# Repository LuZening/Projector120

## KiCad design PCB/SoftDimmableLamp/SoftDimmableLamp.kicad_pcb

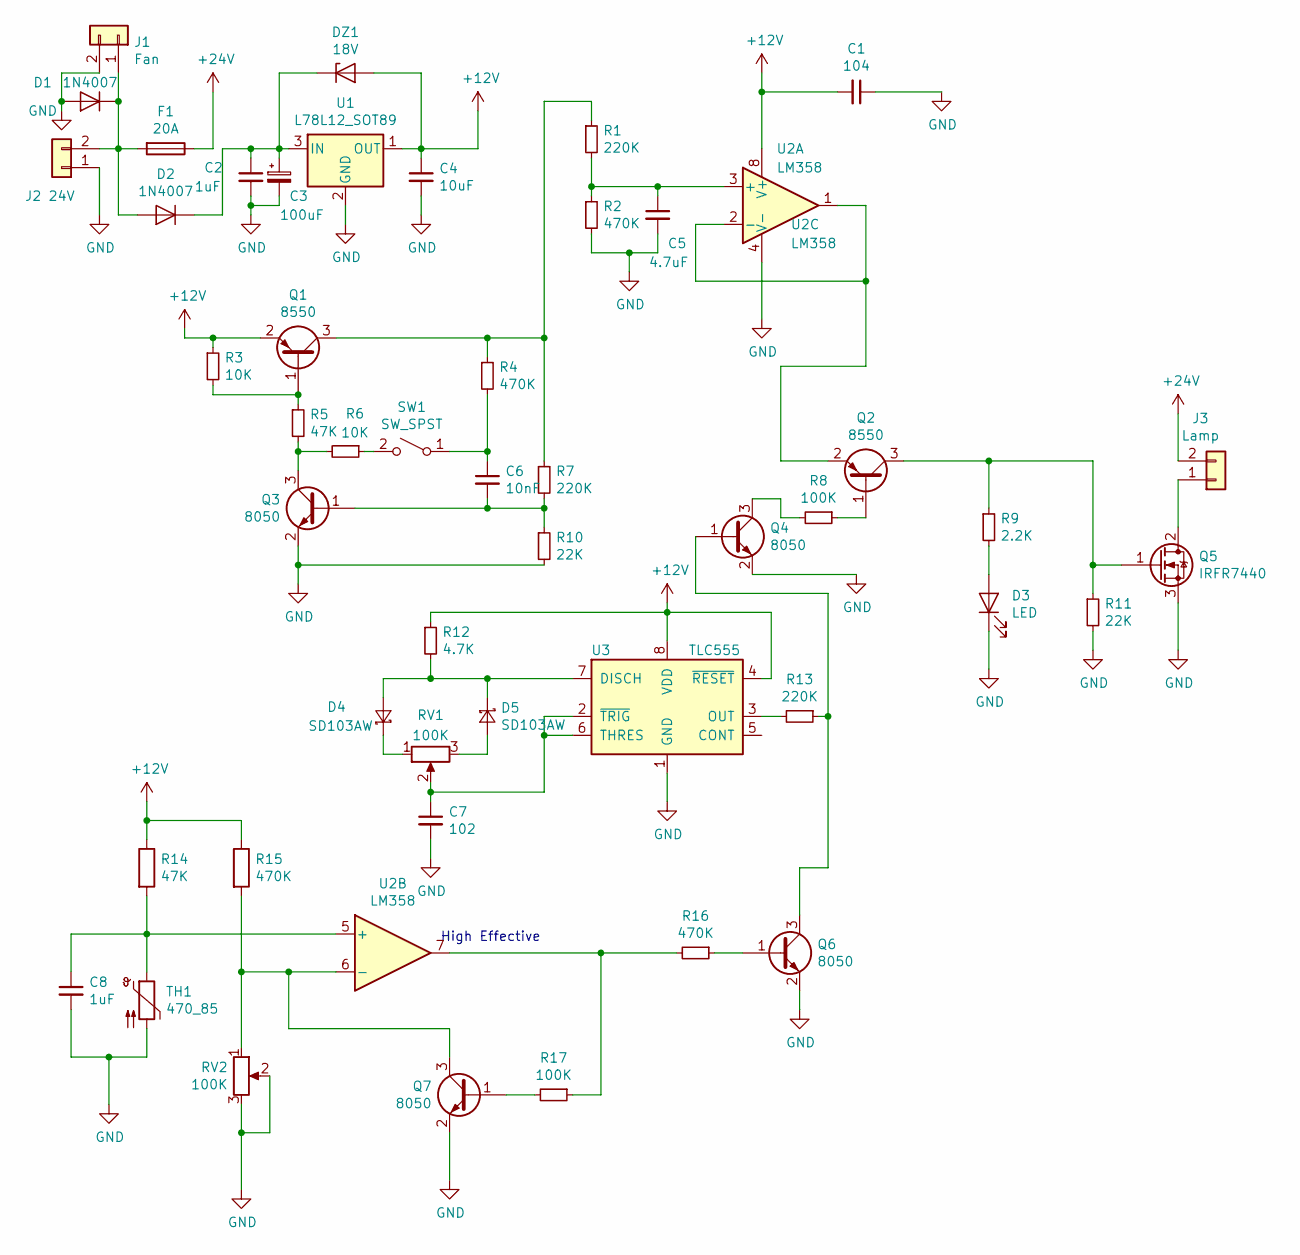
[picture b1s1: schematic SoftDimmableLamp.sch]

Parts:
C1: 104; 0805_C
C2, C8: 1uF; 0805_C
C3: 100uF; CP_Radial_D5.0mm_P2.50mm
C4: 10uF; 0805_C
C5: 4.7uF; 0805_C
C6: 10nF; 0805_C
C7: 102; 0805_C
D1, D2: 1N4007; SMA(DO-214AC)_S2
D3: LED; LED_D3.0mm
D4, D5: SD103AW; SOD-123
DZ1: 18V; LL-34
F1: 20A; FUSE6x32
J1: Fan; Molex_KK-6410-02_02x2.54mm_Straight
J2: 24V; PhoenixContact_GMSTBA-G_02x7.62mm_Angled
J3: Lamp; PhoenixContact_GMSTBA-G_02x7.62mm_Angled
Q1, Q2: 8550; SOT-23(SOT-23-3)
Q3, Q4, Q6, Q7: 8050; SOT-23(SOT-23-3)
Q5: IRFR7440; TO-252-2
R1, R7, R13: 220K; 0805
R2, R4, R15, R16: 470K; 0805
R3, R6: 10K; 0805
R5, R14: 47K; 0805
R8, R17: 100K; 0805
R9: 2.2K; 0805
R10, R11: 22K; 0805
R12: 4.7K; 0805
RV1: 100K; Potentiometer_Alps_RK163_Double_Vertical
RV2: 100K; 3362P
SW1: SW_SPST; PhoenixContact_MSTBA-G_02x5.08mm_Angled
TH1: 470_85; PhoenixContact_MSTBA-G_02x5.08mm_Angled
U1: L78L12_SOT89; SOT-89(SOT-89-3)
U2: LM358; SOIC-8_150MIL
U3: TLC555; SOIC-8_150MIL

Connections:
+12V: C1.2, C4.1, DZ1.1 (A), Q1.2 (E), R3.1, R12.1, R14.1, R15.1, U1.1 (OUT), U2.8 (V+), U3.4 (~RESET), U3.8 (VDD)
+24V: F1.1, J3.2
GND: C1.1, C2.2, C3.2, C4.2, C5.2, C7.2, C8.2, D1.1 (A), D3.1 (K), J1.2, J2.1, Q3.2 (E), Q4.2 (E), Q5.3 (S), Q6.2 (E), Q7.2 (E), R2.2, R10.2, R11.2, RV2.2, RV2.3, TH1.2, U1.2 (GND), U2.4 (V-), U3.1 (GND)
unnamed: C2.1, C3.1, D2.2 (K), DZ1.2 (K), U1.3 (IN)
unnamed: C5.1, R1.2, R2.1, U2.3 (+)
unnamed: C6.1, R4.2, SW1.1 (A)
unnamed: C6.2, Q3.1 (B), R7.2, R10.1
unnamed: C7.1, RV1.2, U3.2 (~TRIG), U3.6 (THRES)
unnamed: C8.1, R14.2, TH1.1, U2.5 (+)
unnamed: D1.2 (K), D2.1 (A), F1.2, J1.1, J2.2
unnamed: D3.2 (A), R9.2
unnamed: D4.1 (A), D5.2 (K), R12.2, U3.7 (DISCH)
unnamed: D4.2 (K), RV1.1
unnamed: D5.1 (A), RV1.3
unnamed: J3.1, Q5.2 (D)
unnamed: Q1.1 (B), R3.2, R5.1
unnamed: Q1.3 (C), R1.1, R4.1, R7.1
unnamed: Q2.1 (B), R8.1
unnamed: Q2.2 (E), U2.1, U2.2 (-)
unnamed: Q2.3 (C), Q5.1 (G), R9.1, R11.1
unnamed: Q3.3 (C), R5.2, R6.2
unnamed: Q4.1 (B), Q6.3 (C), R13.1
unnamed: Q4.3 (C), R8.2
unnamed: Q6.1 (B), R16.1
unnamed: Q7.1 (B), R17.2
unnamed: Q7.3 (C), R15.2, RV2.1, U2.6 (-)
unnamed: R6.1, SW1.2 (B)
unnamed: R13.2, U3.3 (OUT)
unnamed: R16.2, R17.1, U2.7

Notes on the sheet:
High Effective

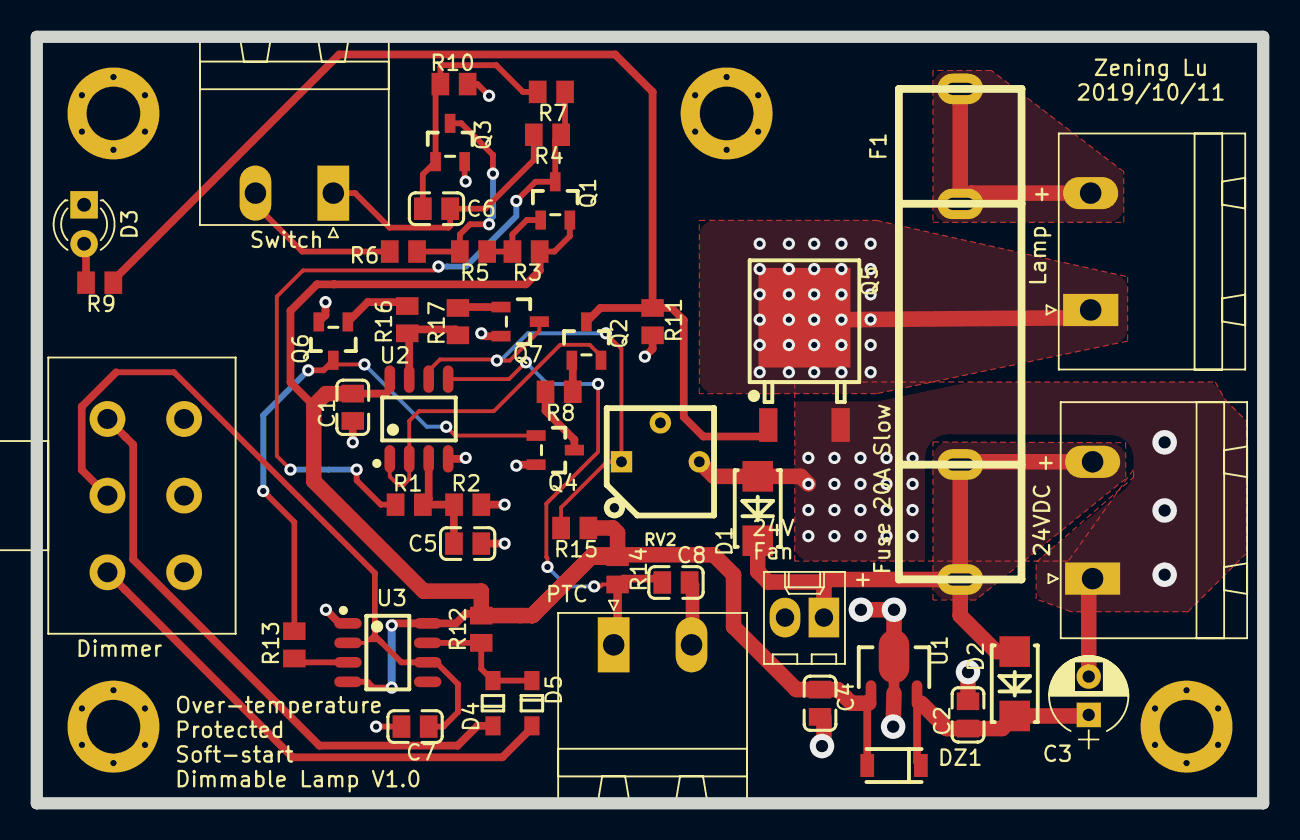
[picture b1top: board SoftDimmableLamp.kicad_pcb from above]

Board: 2 copper layers, 80.0 x 50.0 mm, 49 parts (0 on the bottom side), 29 nets.

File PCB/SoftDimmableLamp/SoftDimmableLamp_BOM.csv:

Comment,Description,Designator,Footprint,LibRef,Pins,Quantity,PartNumber,url
104,desc,"C1,",0805_C,libref,2,1,,
10uF,desc,"C4,",0805_C,libref,2,1,,
4.7uF,desc,"C5,",0805_C,libref,2,1,,
10nF,desc,"C6,",0805_C,libref,2,1,,
102,desc,"C7,",0805_C,libref,2,1,,
1uF,desc,"C8,C2,",0805_C,libref,2,2,,
1N4007,desc,"D1,D2,",SMA(DO-214AC)_S2,libref,2,2,b,
SD103AW,desc,"D5,D4,",SOD-123,libref,2,2,,
18V,desc,"DZ1,",LL-34,libref,2,1,b,
8550,desc,"Q1,Q2,",SOT-23(SOT-23-3),libref,3,2,,
8050,desc,"Q3,Q7,Q6,Q4,",SOT-23(SOT-23-3),libref,3,4,,
IRFR7440,desc,"Q5,",TO-252-2,libref,3,1,b,c
22K,desc,"R10,R11,",805,libref,2,2,,
4.7K,desc,"R12,",805,libref,2,1,,
R,desc,"R15,R14,",805,libref,2,2,,
100K,desc,"R17,R8,",805,libref,2,2,,
470K,desc,"R4,R16,R2,",805,libref,2,3,,
47K,desc,"R5,",805,libref,2,1,,
10K,desc,"R6,R3,",805,libref,2,2,,
220K,desc,"R7,R13,R1,",805,libref,2,3,,
2.2K,desc,"R9,",805,libref,2,1,,
L78L12_SOT89,desc,"U1,",SOT-89(SOT-89-3),libref,4,1,b,c
LM358,desc,"U2,",SOIC-8_150MIL,libref,8,1,b,C
TLC555,desc,"U3,",SOIC-8_150MIL,libref,8,1,,
Through Hole Items ,,,,,,,,
100uF,desc,"C3,",CP_Radial_D5.0mm_P2.50mm,libref,2,1,,
LED,desc,"D3,",LED_D3.0mm,libref,2,1,,
30A,desc,"F1,",FUSE6x32,libref,4,1,b,c
Fan,desc,"J1,",Molex_KK-6410-02_02x2.54mm_Straight,libref,2,1,b,c
24V,desc,"J2,",PhoenixContact_GMSTBA-G_02x7.62mm_Angled,libref,2,1,b,c
Lamp,desc,"J3,",PhoenixContact_GMSTBA-G_02x7.62mm_Angled,libref,2,1,b,c
M3_Screwhole,desc,"REF**,REF**,REF**,REF**,",M3_Screwhole,libref,7,4,,
100K,desc,"RV1,",Potentiometer_Alps_RK163_Double_Vertical,libref,6,1,b,?
100k,desc,"RV2,",3362P,libref,3,1,b,c
SW_SPST,desc,"SW1,",PhoenixContact_MSTBA-G_02x5.08mm_Angled,libref,2,1,b,c
470BE,desc,"TH1,",PhoenixContact_MSTBA-G_02x5.08mm_Angled,libref,2,1,b,c

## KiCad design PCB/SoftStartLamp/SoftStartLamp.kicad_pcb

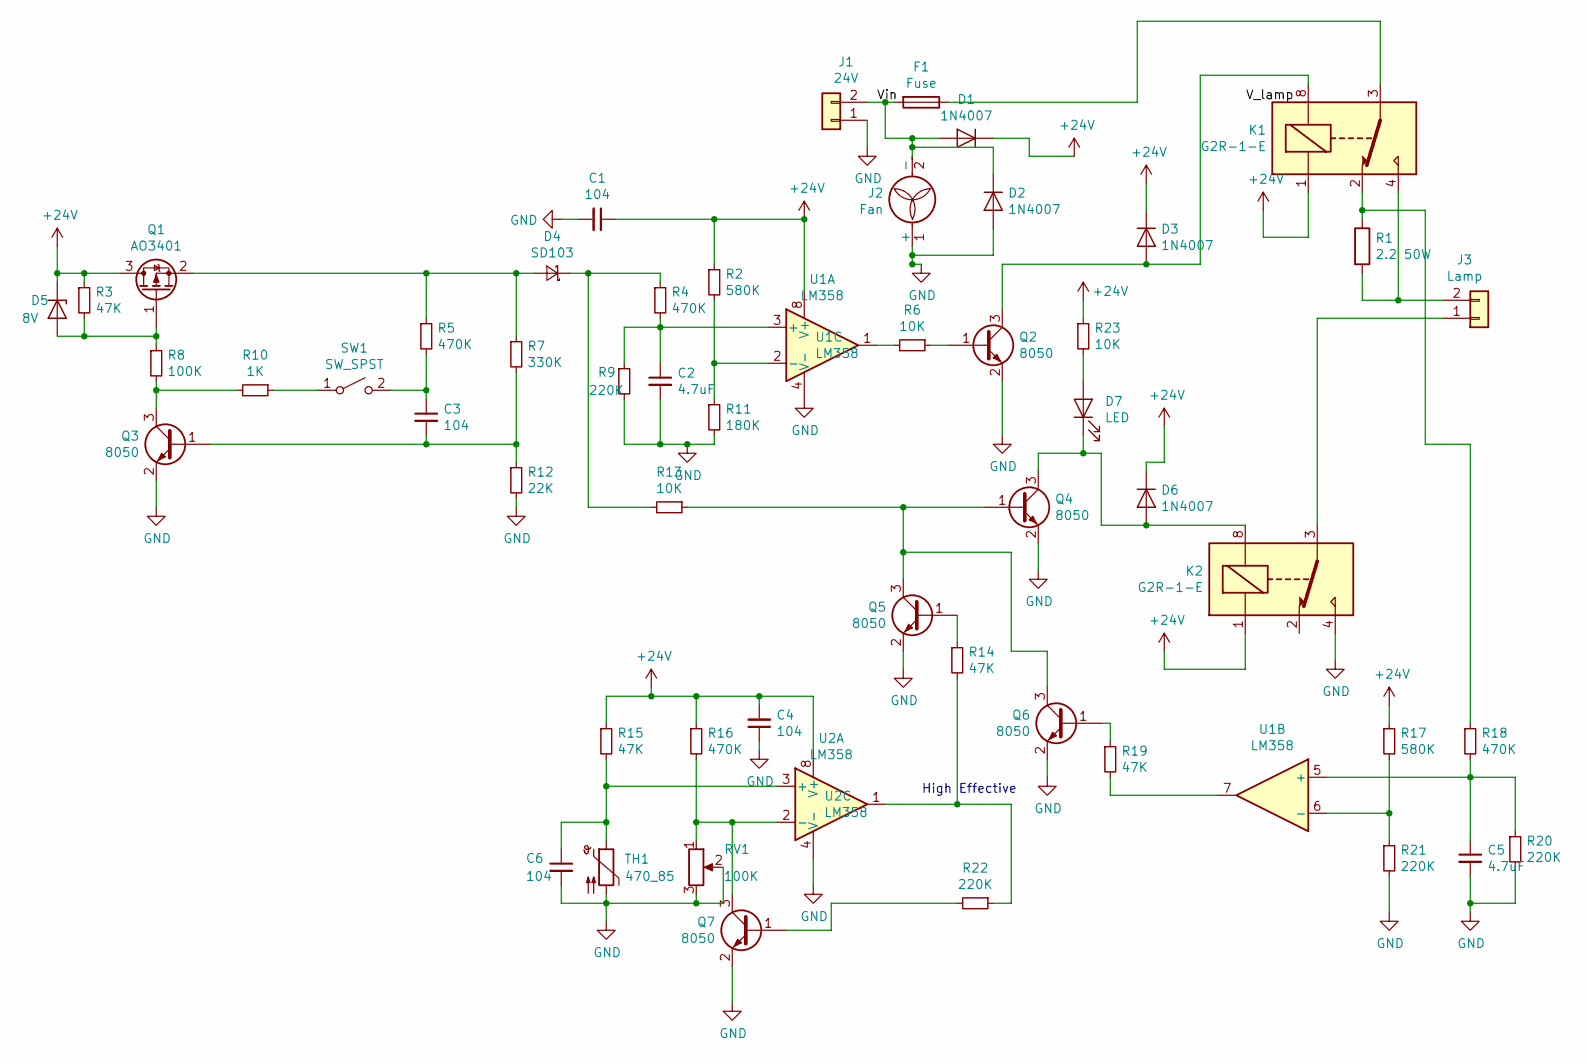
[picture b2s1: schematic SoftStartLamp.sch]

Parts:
C1, C3, C4, C6: 104; 0805
C2, C5: 4.7uF; 0805
D1, D2, D3, D6: 1N4007; SMA(DO-214AC)_S3
D4: SD103; SOD-123
D5: 8V; LL-34
D7: LED; LED_D3.0mm
F1: Fuse; FUSE6x32
J1: 24V; PhoenixContact_GMSTBA-G_02x7.62mm_Angled
J2: Fan; 508CON-2P
J3: Lamp; PhoenixContact_GMSTBA-G_02x7.62mm_Angled
K1, K2: G2R-1-E; OMRON G2R-1-E
Q1: AO3401; SOT-23(SOT-23-3)
Q2, Q3, Q4: 8050; SOT-23(SOT-23-3)
Q5, Q6, Q7: 8050; SOT-23
R1: 2.2 50W; RES50W
R2, R17: 580K; 0805
R3, R14, R15, R19: 47K; 0805
R4, R5, R16, R18: 470K; 0805
R6, R13, R23: 10K; 0805
R7: 330K; 0805
R8: 100K; 0805
R9, R20, R21, R22: 220K; 0805
R10: 1K; 0805
R11: 180K; 0805
R12: 22K; 0805
RV1: 100K; 3362P
SW1: SW_SPST; Molex_KK-6410-02_02x2.54mm_Straight
TH1: 470_85; Molex_KK-6410-02_02x2.54mm_Straight
U1, U2: LM358; SOIC-8_150MIL

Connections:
+24V: C1.1, C4.2, D1.2 (K), D3.2 (K), D5.2 (K), D6.2 (K), K1.1, K2.1, Q1.3 (D), R2.1, R3.1, R15.1, R16.1, R17.1, R23.1, U1.8 (V+), U2.8 (V+)
/Vin: D1.1 (A), D2.2 (K), F1.2, J1.2, J2.2 (-)
GND: C1.2, C2.2, C4.1, C5.2, C6.2, D2.1 (A), J1.1, J2.1 (+), K2.4, K2.5, Q2.2 (E), Q3.2 (E), Q4.2 (E), Q5.2 (E), Q6.2 (E), Q7.2 (E), R9.2, R11.2, R12.2, R20.2, R21.2, RV1.2, RV1.3, TH1.2, U1.4 (V-), U2.4 (V-)
unnamed: C2.1, R4.2, R9.1, U1.3 (+)
unnamed: C3.1, R5.2, SW1.2 (B)
unnamed: C3.2, Q3.1 (B), R7.2, R12.1
unnamed: C5.1, R18.2, R20.1, U1.5 (+)
unnamed: C6.1, R15.2, TH1.1, U2.3 (+)
unnamed: D3.1 (A), K1.8, Q2.3 (C)
unnamed: D4.1 (A), Q1.2 (S), R5.1, R7.1
unnamed: D4.2 (K), R4.1, R13.2
unnamed: D5.1 (A), Q1.1 (G), R3.2, R8.1
unnamed: D6.1 (A), D7.1 (K), K2.8, Q4.3 (C)
unnamed: D7.2 (A), R23.2
unnamed: F1.1, K1.3, K1.6
unnamed: J3.1, K2.3, K2.6
unnamed: J3.2, K1.4, K1.5, R1.2
unnamed: K1.2, K1.7, R1.1, R18.1
unnamed: K2.2, K2.7
unnamed: Q2.1 (B), R6.1
unnamed: Q3.3 (C), R8.2, R10.2
unnamed: Q4.1 (B), Q5.3 (C), Q6.3 (C), R13.1
unnamed: Q5.1 (B), R14.1
unnamed: Q6.1 (B), R19.1
unnamed: Q7.1 (B), R22.2
unnamed: Q7.3 (C), R16.2, RV1.1, U2.2 (-)
unnamed: R6.2, U1.1
unnamed: R10.1, SW1.1 (A)
unnamed: R2.2, R11.1, U1.2 (-)
unnamed: R14.2, R22.1, U2.1
unnamed: R17.2, R21.1, U1.6 (-)
unnamed: R19.2, U1.7

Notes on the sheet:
High Effective

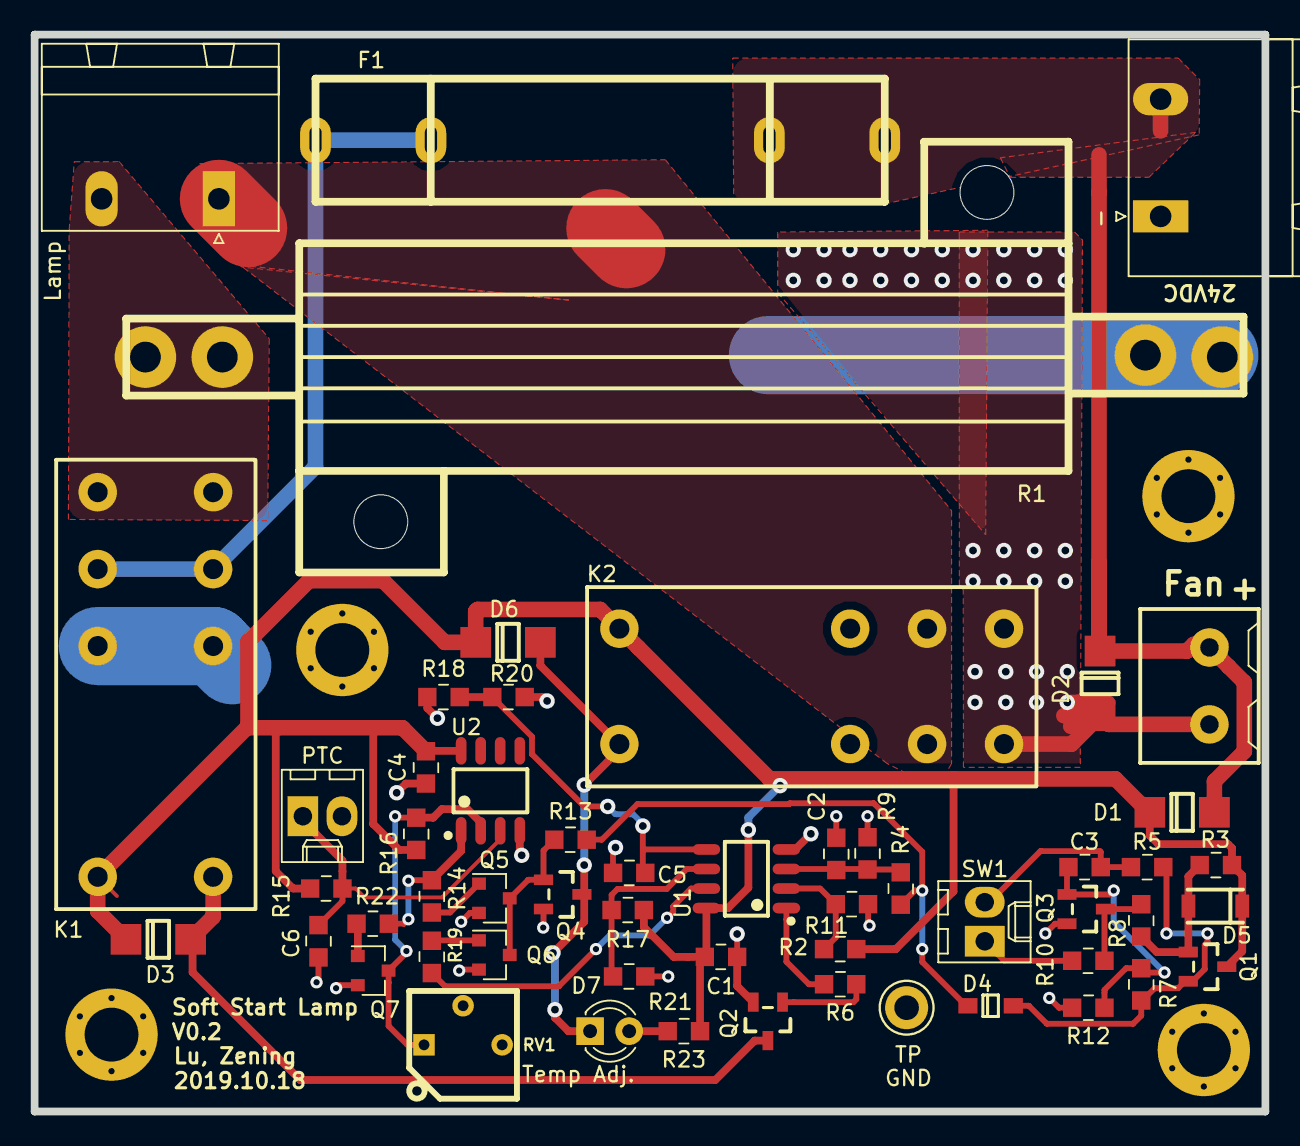
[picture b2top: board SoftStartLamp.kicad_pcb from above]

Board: 2 copper layers, 80.0 x 70.0 mm, 55 parts (0 on the bottom side), 32 nets.

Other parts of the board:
1: M3_Screwhole

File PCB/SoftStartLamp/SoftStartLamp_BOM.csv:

"Comment","Description","Designator","Footprint","LibRef","Pins","Quantity","PartNumber","url",
"4.7uF","desc","C5,C2,","0805","libref","2","2","","",
"104","desc","C6,C4,C3,C1,","0805","libref","2","4","","",
"SD103","desc","D4,","SOD-123","libref","2","1","","",
"8V","desc","D5,","LL-34","libref","2","1","","",
"1N4007","desc","D6,D3,D2,D1,","SMA(DO-214AC)_S3","libref","2","4","","",
"AO3401","desc","Q1,","SOT-23(SOT-23-3)","libref","3","1","","",
"2N5551","desc","Q7,Q6,Q5,","SOT-23","libref","3","3","","",
"2N5401","desc","Q8,","SOT-23(SOT-23-3)","libref","3","1","","",
"2N5551","desc","Q9,Q4,Q3,Q2,","SOT-23(SOT-23-3)","libref","3","4","","",
"1K","desc","R10,","0805","libref","2","1","","",
"180K","desc","R11,","0805","libref","2","1","","",
"22K","desc","R12,","0805","libref","2","1","","",
"4.7K","desc","R13,","0805","libref","2","1","","",
"47K","desc","R15,R19,R14,R3,","0805","libref","2","4","","",
"580K","desc","R17,R2,","0805","libref","2","2","","",
"220K","desc","R22,R21,R20,R9,","0805","libref","2","4","","",
"10K","desc","R23,","0805","libref","2","1","","",
"470K","desc","R26,R25,R24,R18,R16,R5,R4,","0805","libref","2","7","","",
"4.7k","desc","R6,","0805","libref","2","1","","",
"330K","desc","R7,","0805","libref","2","1","","",
"100K","desc","R8,","0805","libref","2","1","","",
"LM358","desc","U2,U1,","SOIC-8_150MIL","libref","8","2","","",
"Through Hole Items ",
"LED","desc","D7,","LED_D3.0mm","libref","2","1","","",
"Fuse","desc","F1,","FUSE6x32","libref","4","1","","",
"24V","desc","J1,","PhoenixContact_GMSTBA-G_02x7.62mm_Angled","libref","2","1","","",
"Fan","desc","J2,","508CON-2P","libref","2","1","","",
"Lamp","desc","J3,","PhoenixContact_GMSTBA-G_02x7.62mm_Angled","libref","2","1","","",
"G2R-1-E","desc","K2,K1,","OMRON G2R-1-E","libref","8","2","","",
"2.2 50W","desc","R1,","RES50W","libref","6","1","","",
"M3_Screwhole","desc","REF**,REF**,1,REF**,","M3_Screwhole","libref","7","4","","",
"Test_Point_Keystone_5005-5009_Compact","desc","REF**,","Test_Point_Keystone_5005-5009_Compact","libref","1","1","","",
"100K","desc","RV1,","3362P","libref","3","1","","",
"SW_SPST","desc","SW1,","Molex_KK-6410-02_02x2.54mm_Straight","libref","2","1","","",
"470_85","desc","TH1,","Molex_KK-6410-02_02x2.54mm_Straight","libref","2","1","","",

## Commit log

2019-10-17 Initialize
2020-10-27 new submission
